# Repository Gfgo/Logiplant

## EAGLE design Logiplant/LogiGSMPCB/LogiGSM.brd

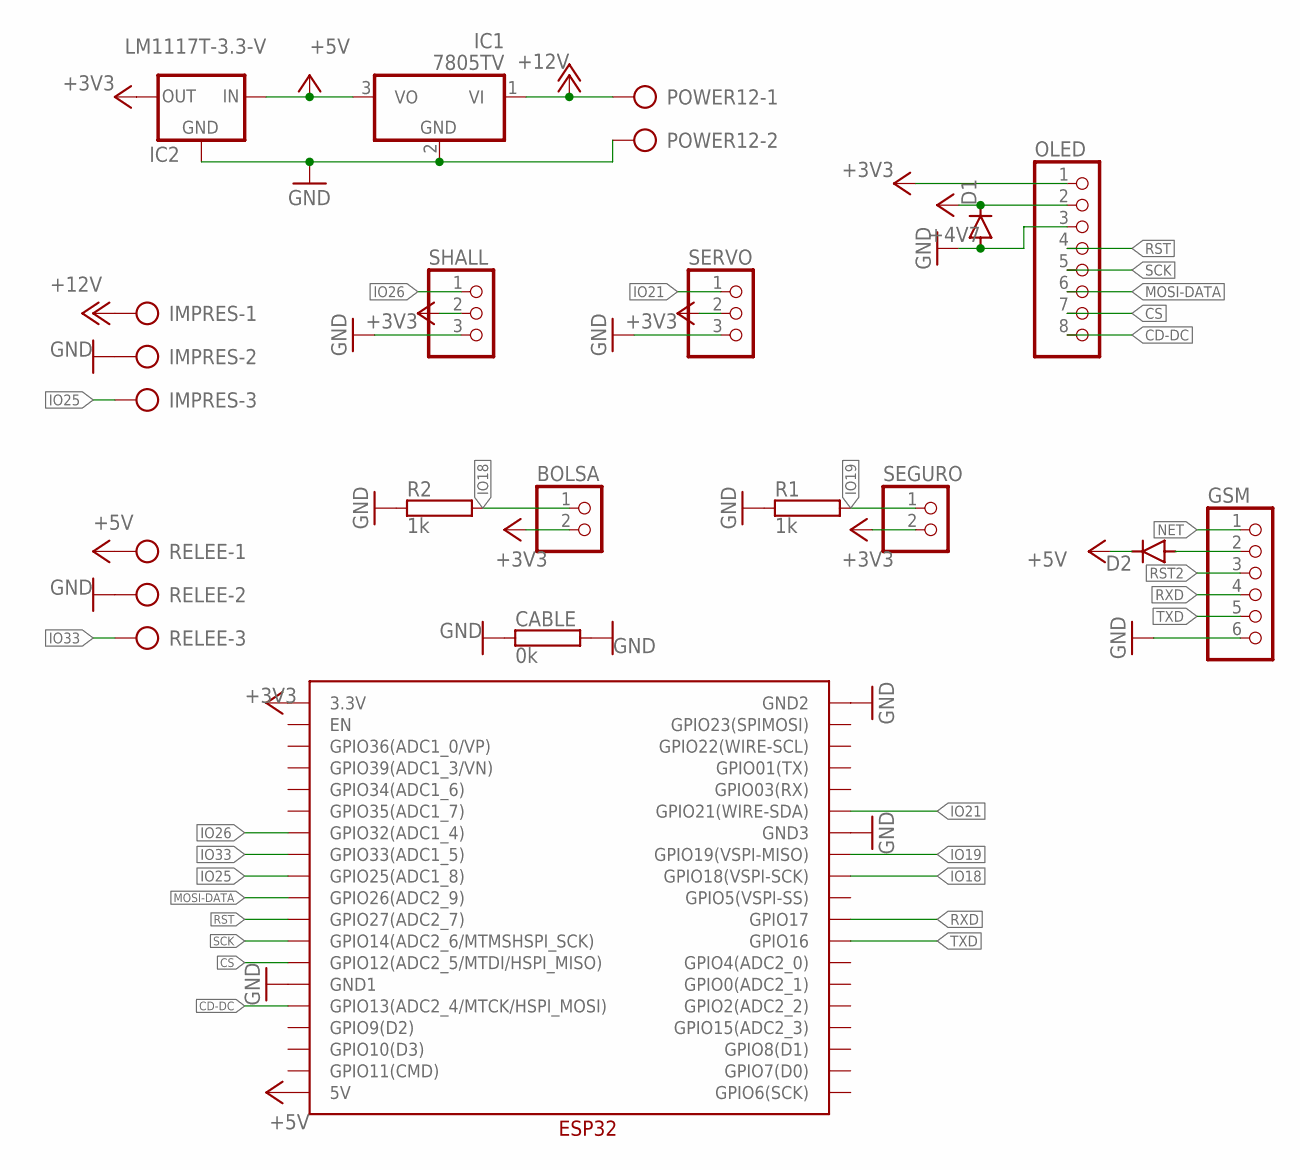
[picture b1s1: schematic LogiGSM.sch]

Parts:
BOLSA: PINHD-1X2; 1X02
CABLE: 0k; RS1/2
D1, D2: DIODE-SOD81; SOD81
GSM: PINHD-1X6; 1X06
IC1: 7805TV; TO220V
IC2: LM1117T-3.3-V; TO220V
IMPRES: AK500/3
OLED: PINHD-1X8; 1X08
POWER12: AK500/2
R1, R2: 1k; RS1/8
RELEE: AK500/3
SEGURO: PINHD-1X2; 1X02
SERVO: PINHD-1X3; 1X03
SHALL: PINHD-1X3; 1X03
U$1: ESP32WESP32W; ESP32W

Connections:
+3V3: BOLSA.2, IC2.2 (OUT), OLED.1, SEGURO.2, SERVO.2, SHALL.2, U$1.3.3V
+5V: D1.C, D2.C, IC1.3 (VO), IC2.3 (IN), OLED.2, RELEE.1, U$1.5V
+12V: IC1.1 (VI), IMPRES.1, POWER12.1
CD-DC: OLED.8, U$1.GPIO13 (GPIO13(ADC2_4/MTCK/HSPI_MOSI))
CS: OLED.7, U$1.GPIO12 (GPIO12(ADC2_5/MTDI/HSPI_MISO))
GND: CABLE.1, CABLE.2, D1.A, GSM.6, IC1.2 (GND), IC2.1 (GND), IMPRES.2, OLED.3, POWER12.2, R1.1, R2.1, RELEE.2, SERVO.3, SHALL.3, U$1.GND1, U$1.GND2, U$1.GND3
IO18: BOLSA.1, R2.2, U$1.GPIO18 (GPIO18(VSPI-SCK))
IO19: R1.2, SEGURO.1, U$1.GPIO19 (GPIO19(VSPI-MISO))
IO21: SERVO.1, U$1.GPIO21 (GPIO21(WIRE-SDA))
IO25: IMPRES.3, U$1.GPIO25 (GPIO25(ADC1_8))
IO26: SHALL.1, U$1.GPIO32 (GPIO32(ADC1_4))
IO33: RELEE.3, U$1.GPIO33 (GPIO33(ADC1_5))
MOSI-DATA: OLED.6, U$1.GPIO26 (GPIO26(ADC2_9))
unnamed: D2.A, GSM.2
NET: GSM.1
RST: OLED.4, U$1.GPIO27 (GPIO27(ADC2_7))
RST2: GSM.3
RXD: GSM.4, U$1.GPIO17
SCK: OLED.5, U$1.GPIO14 (GPIO14(ADC2_6/MTMSHSPI_SCK))
TXD: GSM.5, U$1.GPIO16

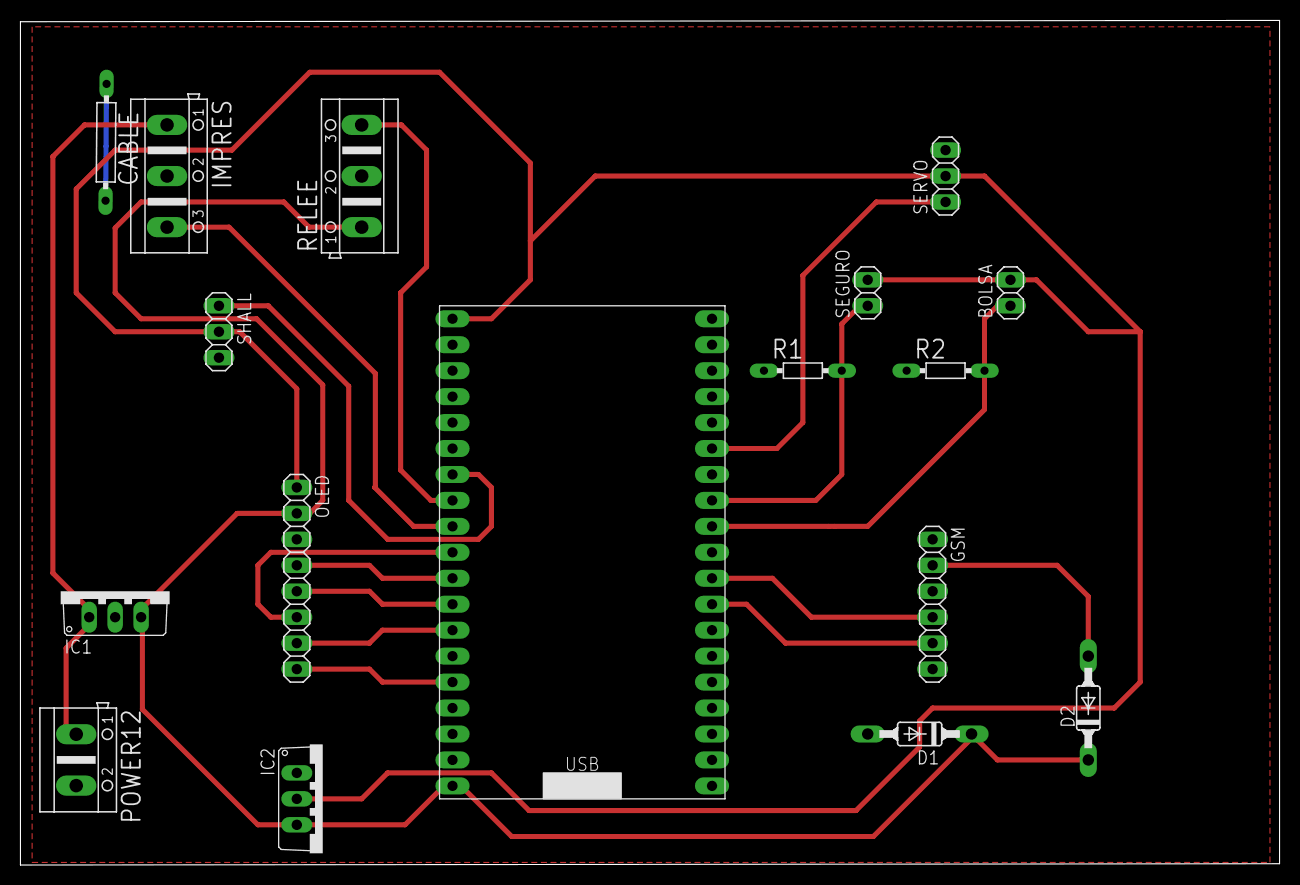
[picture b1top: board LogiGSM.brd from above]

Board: 2 copper layers, 123.2 x 82.7 mm, 17 parts (0 on the bottom side), 18 nets.

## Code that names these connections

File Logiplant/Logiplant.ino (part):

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//#error Bluetooth is not enabled! Please run `make menuconfig` to and enable it
//#endif
//
//#define LED_PIN   32 //GPIO32
//#define LED_COUNT 8
//
//Adafruit_RGBLCDShield lcd = Adafruit_RGBLCDShield();
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
//----------
//------------------------------motor con pir
//byte       motorPin=9;       //GPIO33 Motor
//const int  interval=1000;     //Tiempo
//unsigned long antes=0; 
//byte          pir =3; 
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
Ucglib_SSD1351_18x128x128_FT_SWSPI ucg(/*sclk=*/ 4, /*data=*/ 17, /*cd=*/ 16, /*cs=*/ 0, /*reset=*/ 2);

const byte      servo1Pin = 21;   //GPIO21 Pin SERVO
byte            pos = 0;          //position in degrees
const byte      boton=19;         //GPIO19 Boton de puerta
byte            lecbot=0;         //Lectura estado boton
byte            numbot=0;         //Numero de veces boton pulsado
byte            numbol=0;         //Numero de bolsas
byte            conta=0;
const byte      seguro=18;        //GPIO18 Seguro puerta
byte            lecseg=0;         //Lectura estado seguro
const int       motorPin=33;      //GPIO33 Motor
unsigned long   antes=0;
const long      interval=5000;    //Tiempo en milesimas
const byte      tmol=20;          //Tiempo de molido en segundos
const int       boton2=25;        //GPIO25 Boton de recibo
int             lecbot2=0;        //Lectura estado boton
int             hall= 26;         //GPIO26 sensor hall
int             impresion=27;     //Indicador de impresion

Servo mervo;                      //datos servo en 21
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#define seguropin   19      //junto esp seguro bolsa final carrera
#define bolsapin    18      //junto gsm boton pin bolsa

byte relepin=33;  //GPIO33 pin rele3
byte numbot=0;
byte numbol=1;

int             impresion=27;     //Indicador de impresion
int             hall= 26;         //GPIO26 sensor hall
unsigned long   antes=0;
const long      interv=5000;      //Tiempo en milesimas
bool inicio=false;
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char payload[300];                                    //ubidots
char topic[40];                                       //ubidots

byte relepin=33;  //GPIO33 pin rele3
byte numbot=0;
byte numbol=1;

int             impresion=27;       //Indicador de impresion
int             hall= 26;           //GPIO26 sensor hall
unsigned long   antes=0;
const long      interv=5000;        //Tiempo en milesimas
bool inicio=false;
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
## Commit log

2022-08-02 Create Logiplant.ino
    Inicio
2022-08-10 Update Logiplant.ino
    Distancia y vibración
2023-06-20 Nuevo programa
2023-07-26 Cambio de oled
2023-09-12 Nueva regulación
2023-10-25 Nuevo prog
2023-10-26 Update Logiplant.ino
    Nuevo prog 25/10
2023-10-30 Update Logiplant.ino
    Actualización de programa falta probar todo ok y pantalla.
2023-10-31 Nuevo circuito
    Nuevo circuito
2023-11-08 circuito nuevo
    circuito
2023-11-22 Cambios PCB
2023-11-23 Actualización circuito
2024-05-22 actualización 22/05
2024-08-02 Problemas con interrupcion
    Problemas con interrupcion
2024-08-14 cambios en codigo
    cambios en codigo
2024-08-16 Update Logiplant.ino
    Botón para dar inicio ok
2024-08-16 16/08/2024 tanque lleno tiene problemas
    Seguro motor ok pero seguro tanque lleno tiene problemas
2024-08-20 Update Logiplant.ino
    seguros ok falta gsm pantalla 20/08
2024-08-21 21/08/2024 pantalla
    21/08/2024 pantalla
2024-08-22 arreglando pantalla 22/08/2024
    arreglando pantalla 22/08/2024
2024-08-23 23/08/2024
    23/08/2024 arreglar pantalla
2024-08-26 26/08/2024 arreglando pantalla
    26/08/2024 arreglando pantalla
2024-08-27 27/08/2024 falta texto
    27/08/2024 falta texto
2024-08-28 28/08/2024
    28/08/2024 PROBLEMA CON SEGUROS
2024-08-29 29/082024 problemas con programa
    29/082024 problemas con programa
2024-08-30 30/08/2024 modificar pantalla y problemas con final carrera
    30/08/2024 modificar pantalla y problemas con final carrera
2024-09-02 letras pantalla02/09/2024 pantalla e internet
    letras pantalla02/09/2024 pantalla e internet
2024-09-03 gsm y pantalla falta pruebas 03/09/2024
    gsm y pantalla falta pruebas 03/09/2024
2024-09-05 03/09/2024 gsm y pantalla falta pruebas
    03/09/2024 gsm y pantalla falta pruebas
2024-11-28 28/11/2024
    28/11/2024 Cambios en circuito
2024-12-04 3/12/2024
    3/12/2024actualizacion codigo
